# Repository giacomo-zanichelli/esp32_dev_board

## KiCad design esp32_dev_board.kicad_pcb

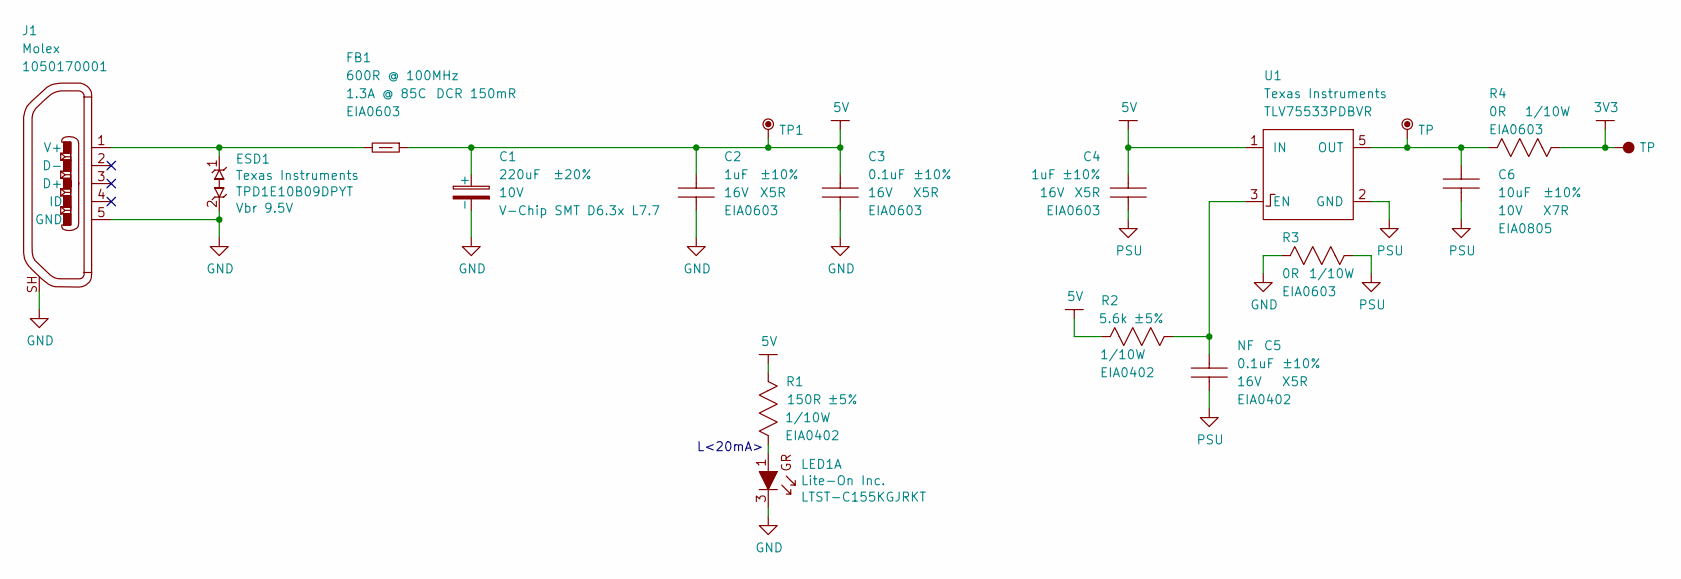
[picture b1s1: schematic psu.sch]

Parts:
C1: WE-865080245009; WE-86508xx450xx_CAPAE660X770D730L255X65N; Tolerance ±20%; Voltage 10V; MPN 865080245009
C2, C4: CAP-EIA0603; CAPC160X80X95L35N; Tolerance ±10%; Voltage 16V; MPN C0603C105K4PACTU
C3: CAP-EIA0603; CAPC160X80X95L35N; Tolerance ±10%; Voltage 16V; MPN C0603C104K4PACTU
C5: CAP-EIA0402; CAPC100X50X55L30N; Tolerance ±10%; Voltage 16V; MPN C0402C104K4PACTU
C6: CAP-EIA0805; CAPC200X125X110L50N; Tolerance ±10%; Voltage 10V; MPN C0805C106K8RACTU
ESD1: TI-TPD1E10B09DPYT; TI-TPD1E10B09DPYT_DIODFN2_100X60X45L25X50N; Breakdown Voltage Vbr 9.5V; MPN TPD1E10B09DPYT
FB1: FB-EIA0603; BEADC160X80X95L40N; MPN BLM18KG601SN1D
J1: Molex-1050170001; MPN 1050170001
LED1: LiteOn-LTST-C155KGJRKT; LiteOn-LTST-C155_LEDCAV4P138_270X320X110L50X90N; MPN LTST-C155KGJRKT
R1: RES-EIA0402; RESC100X50X40L25NN; Tolerance ±5%; Voltage N/A; MPN ERJ2GEJ151X
R2: RES-EIA0402; RESC100X50X40L25NN; Tolerance ±5%; Voltage N/A; MPN ERJ2GEJ562X
R3, R4: RES-EIA0603; RESC160X85X55L30N; Tolerance N/A; Voltage N/A; MPN ERJ3GEY0R00V
TP, TP1: Test-Point-THT; TestPoint-THT_C150H100
U1: TI-TLV75533PDBVR; TI-TLV755_SOT23-5P95_280X145L45X40N; MPN TLV75533PDBVR

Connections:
3V3: R4.2, TP.1; also elsewhere on the board
5V: C1.1 (+), C2.1, C3.1, C4.1, FB1.2, R1.2, R2.2, TP1.1, U1.1 (IN)
GND: C1.2 (-), C2.2, C3.2, ESD1.2, J1.5 (GND), J1.SH, LED1.3 (C), R3.1; also elsewhere on the board
unnamed: C5.1, R2.1, U1.3 (EN)
unnamed 47: C6.1, R4.1, TP.1, U1.5 (OUT); also elsewhere on the board
unnamed: ESD1.1, FB1.1, J1.1 (V+)
unnamed: LED1.1 (A), R1.1
PSU: C4.2, C5.2, C6.2, R3.2, U1.2 (GND)

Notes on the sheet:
L<20mA>

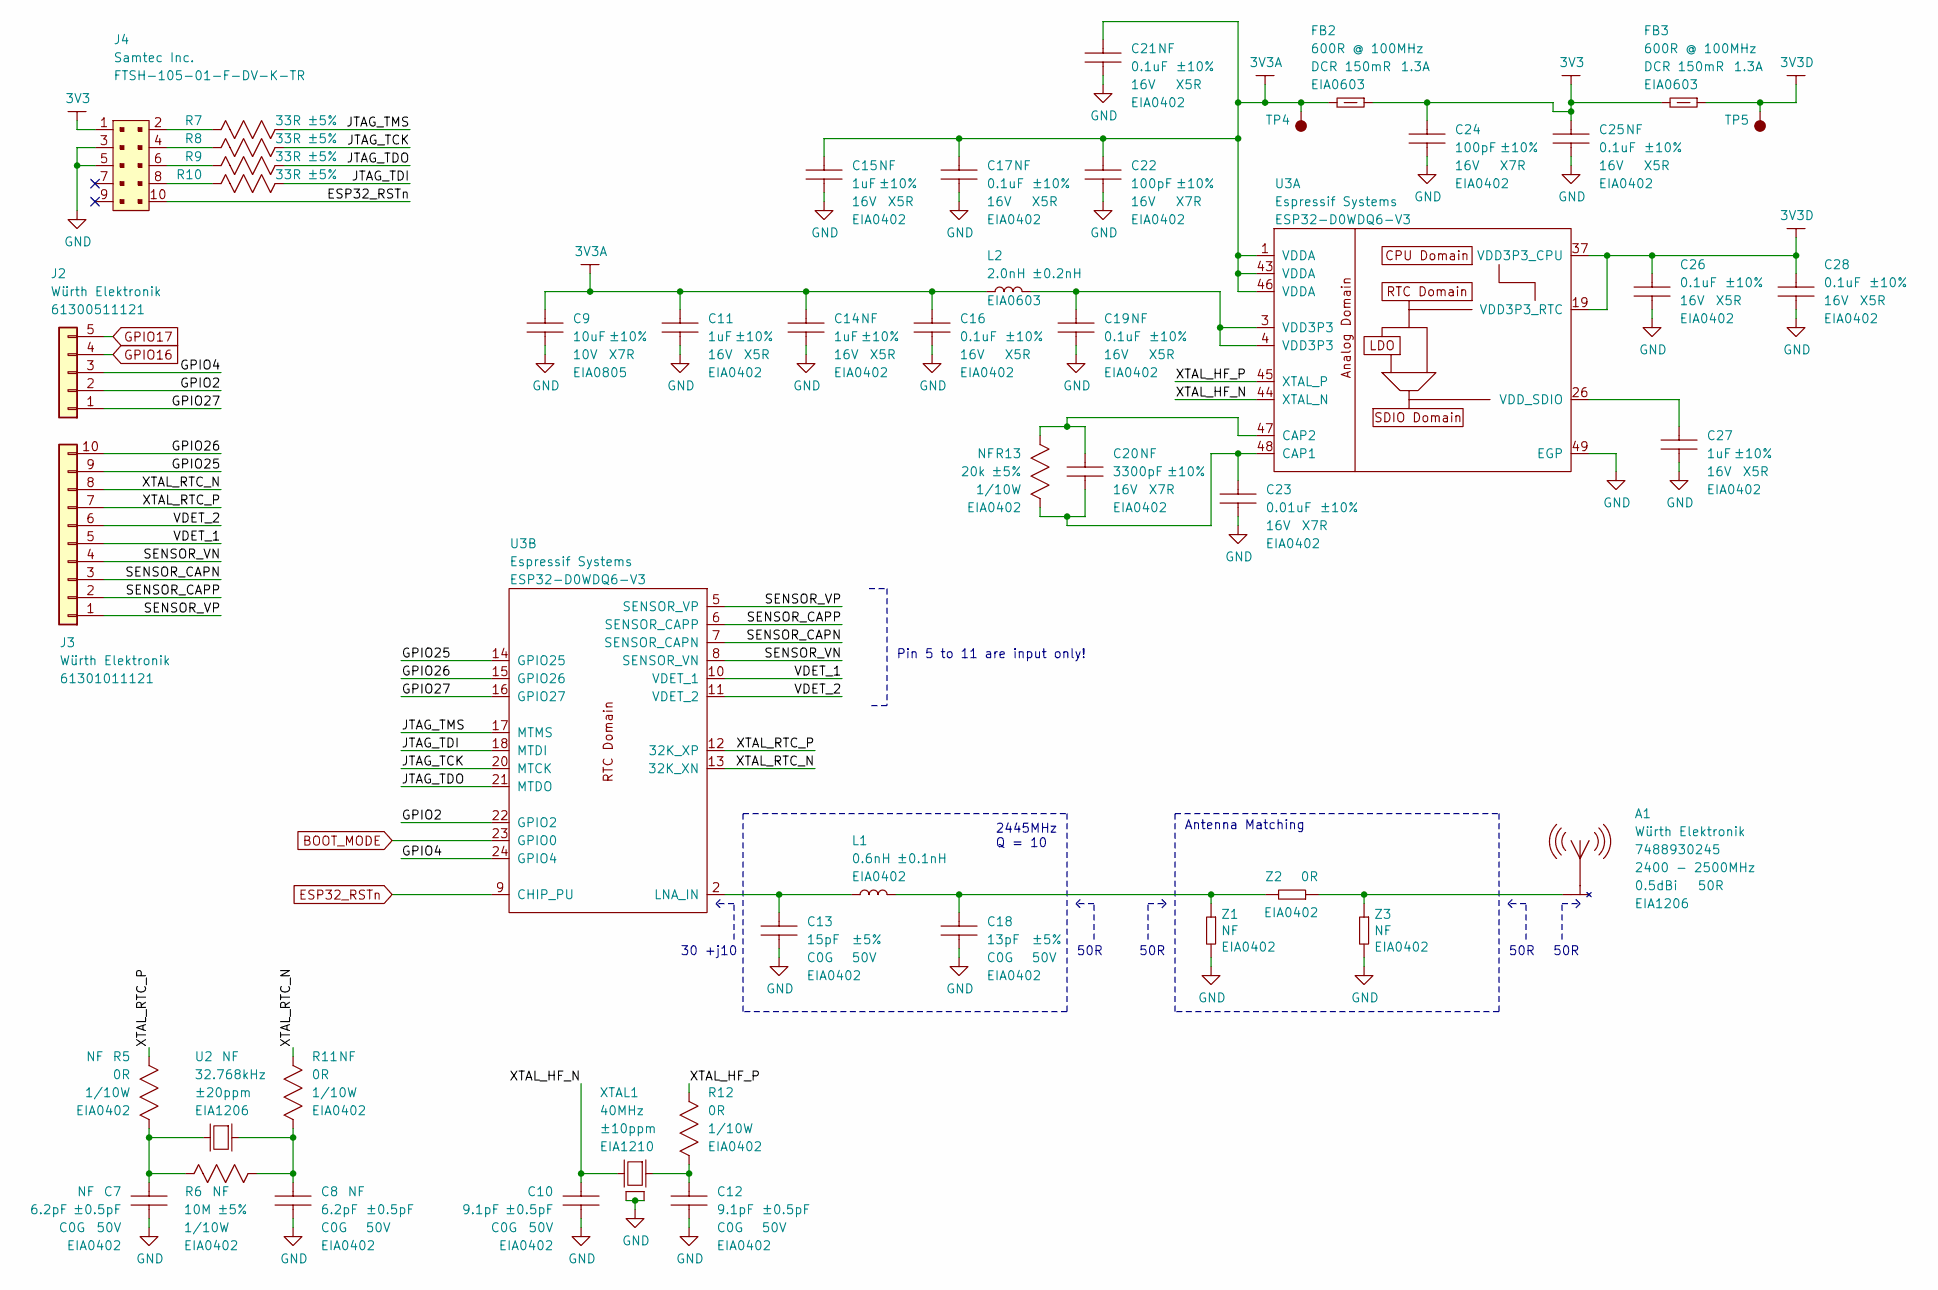
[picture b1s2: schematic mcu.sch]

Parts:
A1: WE-7488930245; WE-7488930245_ANTC320X160X140L50N; MPN 7488930245
C7, C8, C10, C12: CAP-EIA0402; CAPC100X50X55L30N; Tolerance ±0.5pF; Voltage 50V; MPN C0402C919D5GACTU
C9: CAP-EIA0805; CAPC200X125X110L50N; Tolerance ±10%; Voltage 10V; MPN C0805C106K8RACTU
C11, C14, C15, C27: CAP-EIA0402; CAPC100X50X55L30N; Tolerance ±10%; Voltage 16V; MPN C0402C105K4PACTU
C13: CAP-EIA0402; CAPC100X50X55L30N; Tolerance ±5%; Voltage 50V; MPN C0402C150J5GACTU
C16, C17, C19, C21, C25, C26, C28: CAP-EIA0402; CAPC100X50X55L30N; Tolerance ±10%; Voltage 16V; MPN C0402C104K4PACTU
C18: CAP-EIA0402; CAPC100X50X55L30N; Tolerance ±5%; Voltage 50V; MPN C0402C130J5GACTU
C20: CAP-EIA0402; CAPC100X50X55L30N; Tolerance ±10%; Voltage 16V; MPN C0402C332K4RACTU
C22, C24: CAP-EIA0402; CAPC100X50X55L30N; Tolerance ±10%; Voltage 16V; MPN C0402C101K4RACTU
C23: CAP-EIA0402; CAPC100X50X55L30N; Tolerance ±10%; Voltage 16V; MPN C0402C103K4RACTU
FB2, FB3: FB-EIA0603; BEADC160X80X95L40N; MPN BLM18KG601SN1#
J2: WE-61300511121; WE-61300511121_HDRV5W79P254_5X1_1270X254H854; MPN 61300511121
J3: WE-61301011121; WE-61301011121_HDRV10W64P254_10X1_2540X254X884N; MPN 61301011121
J4: Samtec-FTSH-105-01-F-DV-K-TR; Samtec_FTSH-105-01-F-DV-K-TR; MPN FTSH-105-01-F-DV-K-TR
L1: IND-EIA0402; INDC100X50X55L25N; Tolerance ±0.1nH; MPN MLG1005S0N6BT000
L2: IND-EIA0603; INDC160X80X95L40N; Tolerance ±0.2nH; MPN LQP03HQ2N0C02D
R5, R11, R12: RES-EIA0402; RESC100X50X40L25NN; Tolerance N/A; Voltage N/A; MPN ERJ2GE0R00X
R6: RES-EIA0402; RESC100X50X40L25NN; Tolerance ±5%; Voltage N/A; MPN ERJ2GEJ106X
R7, R8, R9, R10: RES-EIA0402; RESC100X50X40L25NN; Tolerance ±5%; Voltage N/A; MPN ERJ2GEJ330X
R13: RES-EIA0402; RESC100X50X40L25NN; Tolerance ±5%; Voltage N/A; MPN ERJ2GEJ203X
TP4, TP5: Test-Point-SMT; TestPoint-SMT_C100
U2: RaltronElectronics-RT3215-32.768-6-TR; RaltronElectronics-RT3215_XTALDFN2_320X150X90L65X130N; Tolerance ±20ppm; MPN RT3215-32.768-6-TR
U3: Espressif_ESP32-D0WDQ6-V3; Espressif-ESP32_QFN49P40_600X600X90L40X20T430N; MPN ESP32-D0WDQ6-V3
XTAL1: RaltronElectronics-RH100-40.000-9-F-1010-EXT-TR; RaltronElectronics-RH100_XTALDFN4_250X320X80L90X100N; Tolerance ±10ppm; MPN RH100-40.000-9-F-1010-EXT-TR
Z1, Z2, Z3: Z-EIA0402; RESC100X50X40L25NN; Tolerance TBD; MPN TBD

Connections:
3V3: C24.1, C25.1, FB2.2, FB3.1, J4.1; also elsewhere on the board
3V3A: C9.1, C11.1, C14.1, C15.1, C16.1, C17.1, C21.1, C22.1, FB2.1, L2.1, TP4.1, U3.1 (VDDA), U3.43 (VDDA), U3.46 (VDDA)
3V3D: C26.1, C28.1, FB3.2, TP5.1, U3.19 (VDD3P3_RTC), U3.37 (VDD3P3_CPU)
/MCU/GPIO2: J2.2, U3.22 (GPIO2)
/MCU/GPIO4: J2.3, U3.24 (GPIO4)
/MCU/GPIO25: J3.9, U3.14 (GPIO25)
/MCU/GPIO26: J3.10, U3.15 (GPIO26)
/MCU/GPIO27: J2.1, U3.16 (GPIO27)
/MCU/JTAG_TCK: R8.1, U3.20 (MTCK)
/MCU/JTAG_TDI: R10.1, U3.18 (MTDI)
/MCU/JTAG_TDO: R9.1, U3.21 (MTDO)
/MCU/JTAG_TMS: R7.1, U3.17 (MTMS)
/MCU/SENSOR_CAPN: J3.3, U3.7 (SENSOR_CAPN)
/MCU/SENSOR_CAPP: J3.2, U3.6 (SENSOR_CAPP)
/MCU/SENSOR_VN: J3.4, U3.8 (SENSOR_VN)
/MCU/SENSOR_VP: J3.1, U3.5 (SENSOR_VP)
/MCU/VDET_1: J3.5, U3.10 (VDET_1)
/MCU/VDET_2: J3.6, U3.11 (VDET_2)
/MCU/XTAL_HF_N: C10.1, U3.44 (XTAL_N), XTAL1.1
/MCU/XTAL_HF_P: R12.1, U3.45 (XTAL_P)
/MCU/XTAL_RTC_N: J3.8, R11.1, U3.13 (32K_XN)
/MCU/XTAL_RTC_P: J3.7, R5.1, U3.12 (32K_XP)
BOOT_MODE: U3.23 (GPIO0); also elsewhere on the board
ESP32_RSTn: J4.10, U3.9 (CHIP_PU); also elsewhere on the board
GND: C7.2, C8.2, C9.2, C10.2, C11.2, C12.2, C13.2, C14.2, C15.2, C16.2, C17.2, C18.2, C19.2, C21.2, C22.2, C23.2, C24.2, C25.2, C26.2, C27.2, C28.2, J4.3, J4.5, U3.49 (EGP), XTAL1.2, XTAL1.4, Z1.2, Z3.2; also elsewhere on the board
GPIO16: J2.4; also elsewhere on the board
GPIO17: J2.5; also elsewhere on the board
unnamed: A1.1, Z2.1, Z3.1
unnamed: C7.1, R5.2, R6.2, U2.1
unnamed: C8.1, R6.1, R11.2, U2.2
unnamed: C12.1, R12.2, XTAL1.3
unnamed: C13.1, L1.1, U3.2 (LNA_IN)
unnamed: C18.1, L1.2, Z1.1, Z2.2
unnamed: C19.1, L2.2, U3.3 (VDD3P3), U3.4 (VDD3P3)
unnamed: C20.1, C23.1, R13.1, U3.48 (CAP1)
unnamed: C20.2, R13.2, U3.47 (CAP2)
unnamed: C27.1, U3.26 (VDD_SDIO)
unnamed: J4.2, R7.2
unnamed: J4.4, R8.2
unnamed: J4.6, R9.2
unnamed: J4.8, R10.2

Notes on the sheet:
30 +j10
50R
2445MHz Q = 10
Antenna Matching
Pin 5 to 11 are input only!

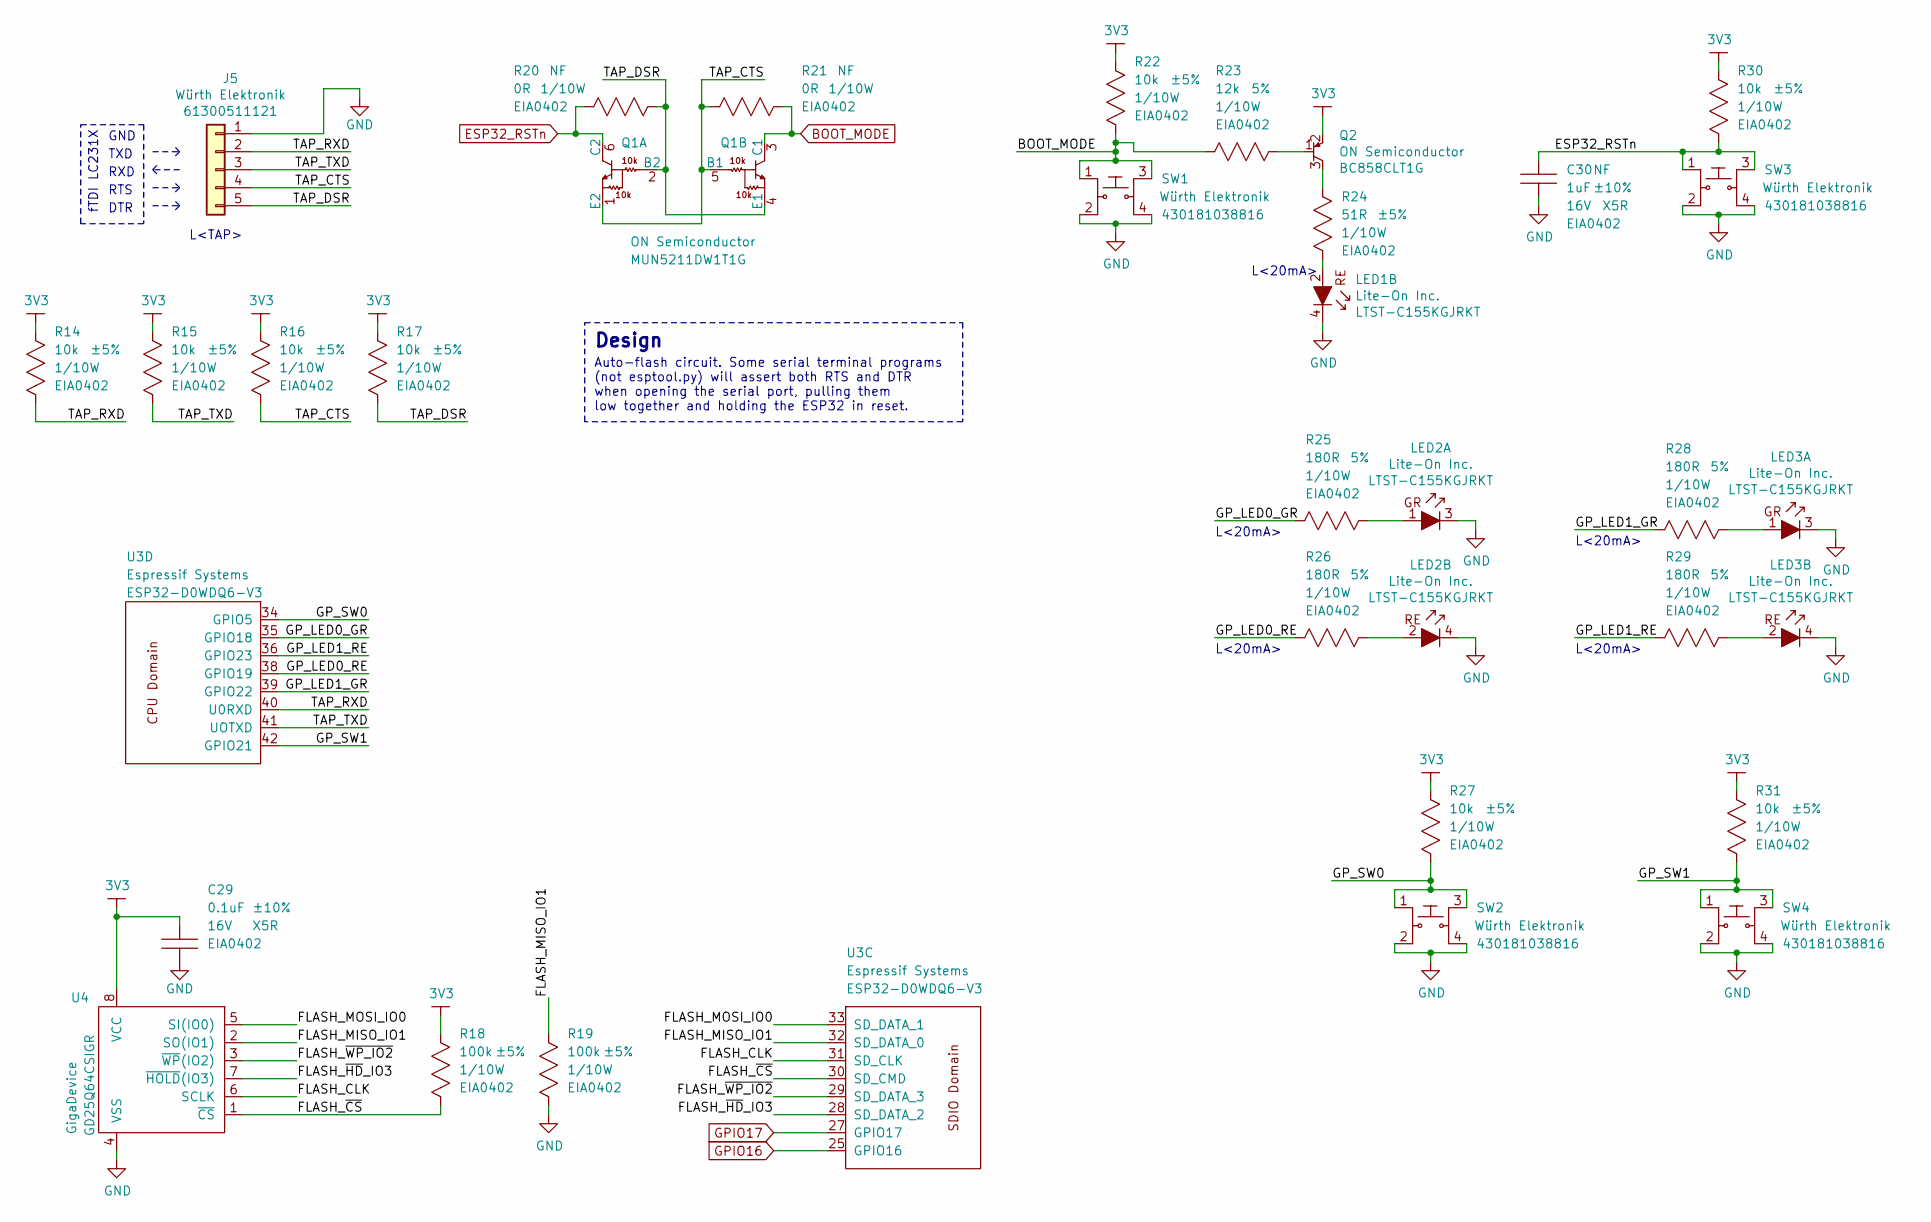
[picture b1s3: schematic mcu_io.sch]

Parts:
C29: CAP-EIA0402; CAPC100X50X55L30N; Tolerance ±10%; Voltage 16V; MPN C0402C104K4PACTU
C30: CAP-EIA0402; CAPC100X50X55L30N; Tolerance ±10%; Voltage 16V; MPN C0402C105K4PACTU
J5: WE-61300511121; WE-61300511121_HDRV5W79P254_5X1_1270X254H854; MPN 61300511121
LED1, LED2, LED3: LiteOn-LTST-C155KGJRKT; LiteOn-LTST-C155_LEDCAV4P138_270X320X110L50X90N; MPN LTST-C155KGJRKT
Q1: ON-Semi_MUN5211DW1T1G; ON-Semi-MUN5211DW1T1G_SOT23-6P65_210X110L36X20L; MPN MUN5211DW1T1G
Q2: ON-Semi_BC858CLT1G; ON-Semi-BC858CLT1G_SOT23-3P85_237X111L42X43N; MPN BC858CLT1G
R14, R15, R16, R17, R22, R27, R30, R31: RES-EIA0402; RESC100X50X40L25NN; Tolerance ±5%; Voltage N/A; MPN ERJ2GEJ103X
R18, R19: RES-EIA0402; RESC100X50X40L25NN; Tolerance ±5%; Voltage N/A; MPN ERJ-2GEJ104X
R20, R21: RES-EIA0402; RESC100X50X40L25NN; Tolerance N/A; Voltage N/A; MPN ERJ2GE0R00X
R23: RES-EIA0402; RESC100X50X40L25NN; Tolerance 5%; Voltage N/A; MPN ERJ2GEJ123X
R24: RES-EIA0402; RESC100X50X40L25NN; Tolerance ±5%; Voltage N/A; MPN ERJ2GEJ510X
R25, R26, R28, R29: RES-EIA0402; RESC100X50X40L25NN; Tolerance 5%; Voltage N/A; MPN ERJ2GEJ181X
SW1, SW2, SW3, SW4: WE-430181038816; WE-430181038816_SWSOFL4P150_450X750X380L150X70N; MPN 430181038816
U3: Espressif_ESP32-D0WDQ6-V3; Espressif-ESP32_QFN49P40_600X600X90L40X20T430N; MPN ESP32-D0WDQ6-V3
U4: GigaDevice-GD25Q64CSIGR; GigaDevice-GD25Q64CS_SOIC8P127_523X790X216L67X41N; MPN GD25Q64CSIGR

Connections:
3V3: C29.1, Q2.2 (E), R14.1, R15.1, R16.1, R17.1, R18.1, R22.1, R27.1, R30.1, R31.1, U4.8 (VCC); also elsewhere on the board
/MCU_IO/FLASH_CLK: U3.31 (SD_CLK), U4.6 (SCLK)
/MCU_IO/FLASH_MISO_IO1: R19.1, U3.32 (SD_DATA_0), U4.2 (SO(IO1))
/MCU_IO/FLASH_MOSI_IO0: U3.33 (SD_DATA_1), U4.5 (SI(IO0))
/MCU_IO/FLASH_~CS~: R18.2, U3.30 (SD_CMD), U4.1 (~CS)
/MCU_IO/FLASH_~HD~_IO3: U3.28 (SD_DATA_2), U4.7 (~HOLD~(IO3))
/MCU_IO/FLASH_~WP_IO2: U3.29 (SD_DATA_3), U4.3 (~WP~(IO2))
/MCU_IO/GP_LED0_GR: R25.1, U3.35 (GPIO18)
/MCU_IO/GP_LED0_RE: R26.1, U3.38 (GPIO19)
/MCU_IO/GP_LED1_GR: R28.1, U3.39 (GPIO22)
/MCU_IO/GP_LED1_RE: R29.1, U3.36 (GPIO23)
/MCU_IO/GP_SW0: R27.2, SW2.1, SW2.3, U3.34 (GPIO5)
/MCU_IO/GP_SW1: R31.2, SW4.1, SW4.3, U3.42 (GPIO21)
/MCU_IO/TAP_CTS: J5.4, Q1.1 (E2), Q1.5 (B1), R16.2, R21.1
/MCU_IO/TAP_DSR: J5.5, Q1.2 (B2), Q1.4 (E1), R17.2, R20.2
/MCU_IO/TAP_RXD: J5.2, R14.2, U3.40 (U0RXD)
/MCU_IO/TAP_TXD: J5.3, R15.2, U3.41 (UOTXD)
BOOT_MODE: Q1.3 (C1), R21.2, R22.2, R23.1, SW1.1, SW1.3; also elsewhere on the board
ESP32_RSTn: C30.1, Q1.6 (C2), R20.1, R30.2, SW3.1, SW3.3; also elsewhere on the board
GND: C29.2, C30.2, J5.1, LED1.4 (C), LED2.3 (C), LED2.4 (C), LED3.3 (C), LED3.4 (C), R19.2, SW1.2, SW1.4, SW2.2, SW2.4, SW3.2, SW3.4, SW4.2, SW4.4, U4.4 (VSS); also elsewhere on the board
GPIO16: U3.25 (GPIO16); also elsewhere on the board
GPIO17: U3.27 (GPIO17); also elsewhere on the board
unnamed: LED1.2 (A), R24.2
unnamed: LED2.1 (A), R25.2
unnamed: LED2.2 (A), R26.2
unnamed: LED3.1 (A), R28.2
unnamed: LED3.2 (A), R29.2
unnamed: Q2.1 (B), R23.2
unnamed: Q2.3 (C), R24.1

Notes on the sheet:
TXD
RXD
RTS
DTR
GND
fTDI LC231X
Design
Auto-flash circuit. Some serial terminal programs (not esptool.py) will assert both RTS and DTR when opening the serial port, pulling them low together and holding the ESP32 in reset.
L<TAP>
L<20mA>

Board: 4 copper layers, 95 parts (0 on the bottom side), 70 nets, no tracks yet.

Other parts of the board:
TP2: Test-Point-THT; TestPoint-THT_C150H100
TP3: Test-Point-SMT; TestPoint-SMT_C100

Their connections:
3V3: TP3.1; also elsewhere on the board
unnamed 47: TP2.1; also elsewhere on the board

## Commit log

2021-02-28 Initialize project esp32_dev_board
2021-03-06 Add ESD protection to USB
2021-03-06 Add FB to power input
2021-03-06 Add e-cap on power rail
2021-03-06 Add 1uF cap to power rail
2021-03-06 Add 0.1uF cap to power rail
2021-03-06 Add TI-TLV75533PDBVR.
2021-03-06 Add *-bak and _autosave* to .gitignore
2021-03-07 Ignore gitaddcommit.sh
2021-03-08 Add LDO output cap.
2021-03-08 Add PSU to GND jumper.
2021-03-08 Add filter cap to LDO EN pin.
2021-03-08 Add PU to LDO EN line.
2021-03-08 Add 3V3 label to LDO output.
2021-03-08 Add 0R jumper to LDO output and move 3V3 label after it.
2021-03-08 Update ceramic capacitors with Vendor, Vendor_Pn, Fit fields following master library update.
2021-03-08 Update symbols in psu.sch with Vendor, Vendor_PN, Fit fields.
2021-03-08 Update ESP32, GigaDevice GD25Q64 with Vendor, Vendor_PN, Fit fields from library.
2021-03-08 Update footprint ref in Molex USB connector.
2021-03-08 Update footprint ref to footprint and footprint_generic library names.
2021-03-08 Update GigaDevice GD25Q64 value.
2021-03-08 Update GigaDevice-GD25Q64CSIGR datasheet ref.
2021-03-08 Update schematic to KEMET and Panasonic passives.
2021-03-09 Add Test points to PSU section.
2021-03-09 Add VDD3P3 pins decoupling and HF harmonics filter.
2021-03-09 Sync repo, no change.
2021-03-10 Conclude PSU section of ESP32.
2021-03-10 Add ESP32 reset line R.
2021-03-10 Add ESP32 reset line C and label.
2021-03-10 Add reset tact switch circuit.
2021-03-10 Add HF XTAL circuit.
2021-03-10 Add RTC crystal circuit.
2021-03-10 Add external capacitor circuit to ESP32 section.
2021-03-10 Sync repo, no changes.
2021-03-11 Add harmonic filter to ESP32 RF front end.
2021-03-13 Add antenna matching section.
2021-03-13 Separate MCU I/O sections in their own sheet.
2021-03-13 Add BOOT_MODE tact switch.
2021-03-13 Add power and boot mode LED's.
2021-03-14 Add TAP interface.
2021-03-15 Add flow control to TAP to auto-flash ESP32.
2021-03-15 Add auto-flash circuit to prevent DTR == 1 && RTS == 1 condition to keep ESP32 in reset.
2021-03-15 Add TAP pull-ups; NF R to bypass auto-flash NPN network.
2021-03-21 Add TAP layout note; move ESP32 boot mode and reset button to I/O sheet.
2021-03-21 Fix Boot Mode LED circuit (add PNP drive); add 2x BiColour general-purpose LED's.
2021-03-21 Add current requirement to Power On LED.
2021-03-21 Add general purpose tact switches.
2021-03-21 Add JTAG interface.
2021-03-28 Bring out on headers all unused ESP32 pins.
2021-03-28 Add antenna.
2021-03-28 Annotate schematic.
2021-03-28 Start layout config.
2021-03-28 Sync at the end of the day.
2021-04-11 Start layout.
2021-04-11 Fix wrong footprint on GigaDevice part (correct in library though).
2021-04-11 Update J4 footprint after removing leading zeros in pad names.
2021-04-11 Annotate test points.
2021-04-11 Update power symbols after change to pin names; annotate.
2021-04-11 Mid-way through placement.
2021-04-11 Update placement.
